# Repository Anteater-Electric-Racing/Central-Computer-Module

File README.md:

# Central Computer Module 

Main embedded firmware board for KZ 2025

## PCB Render

## Schematic

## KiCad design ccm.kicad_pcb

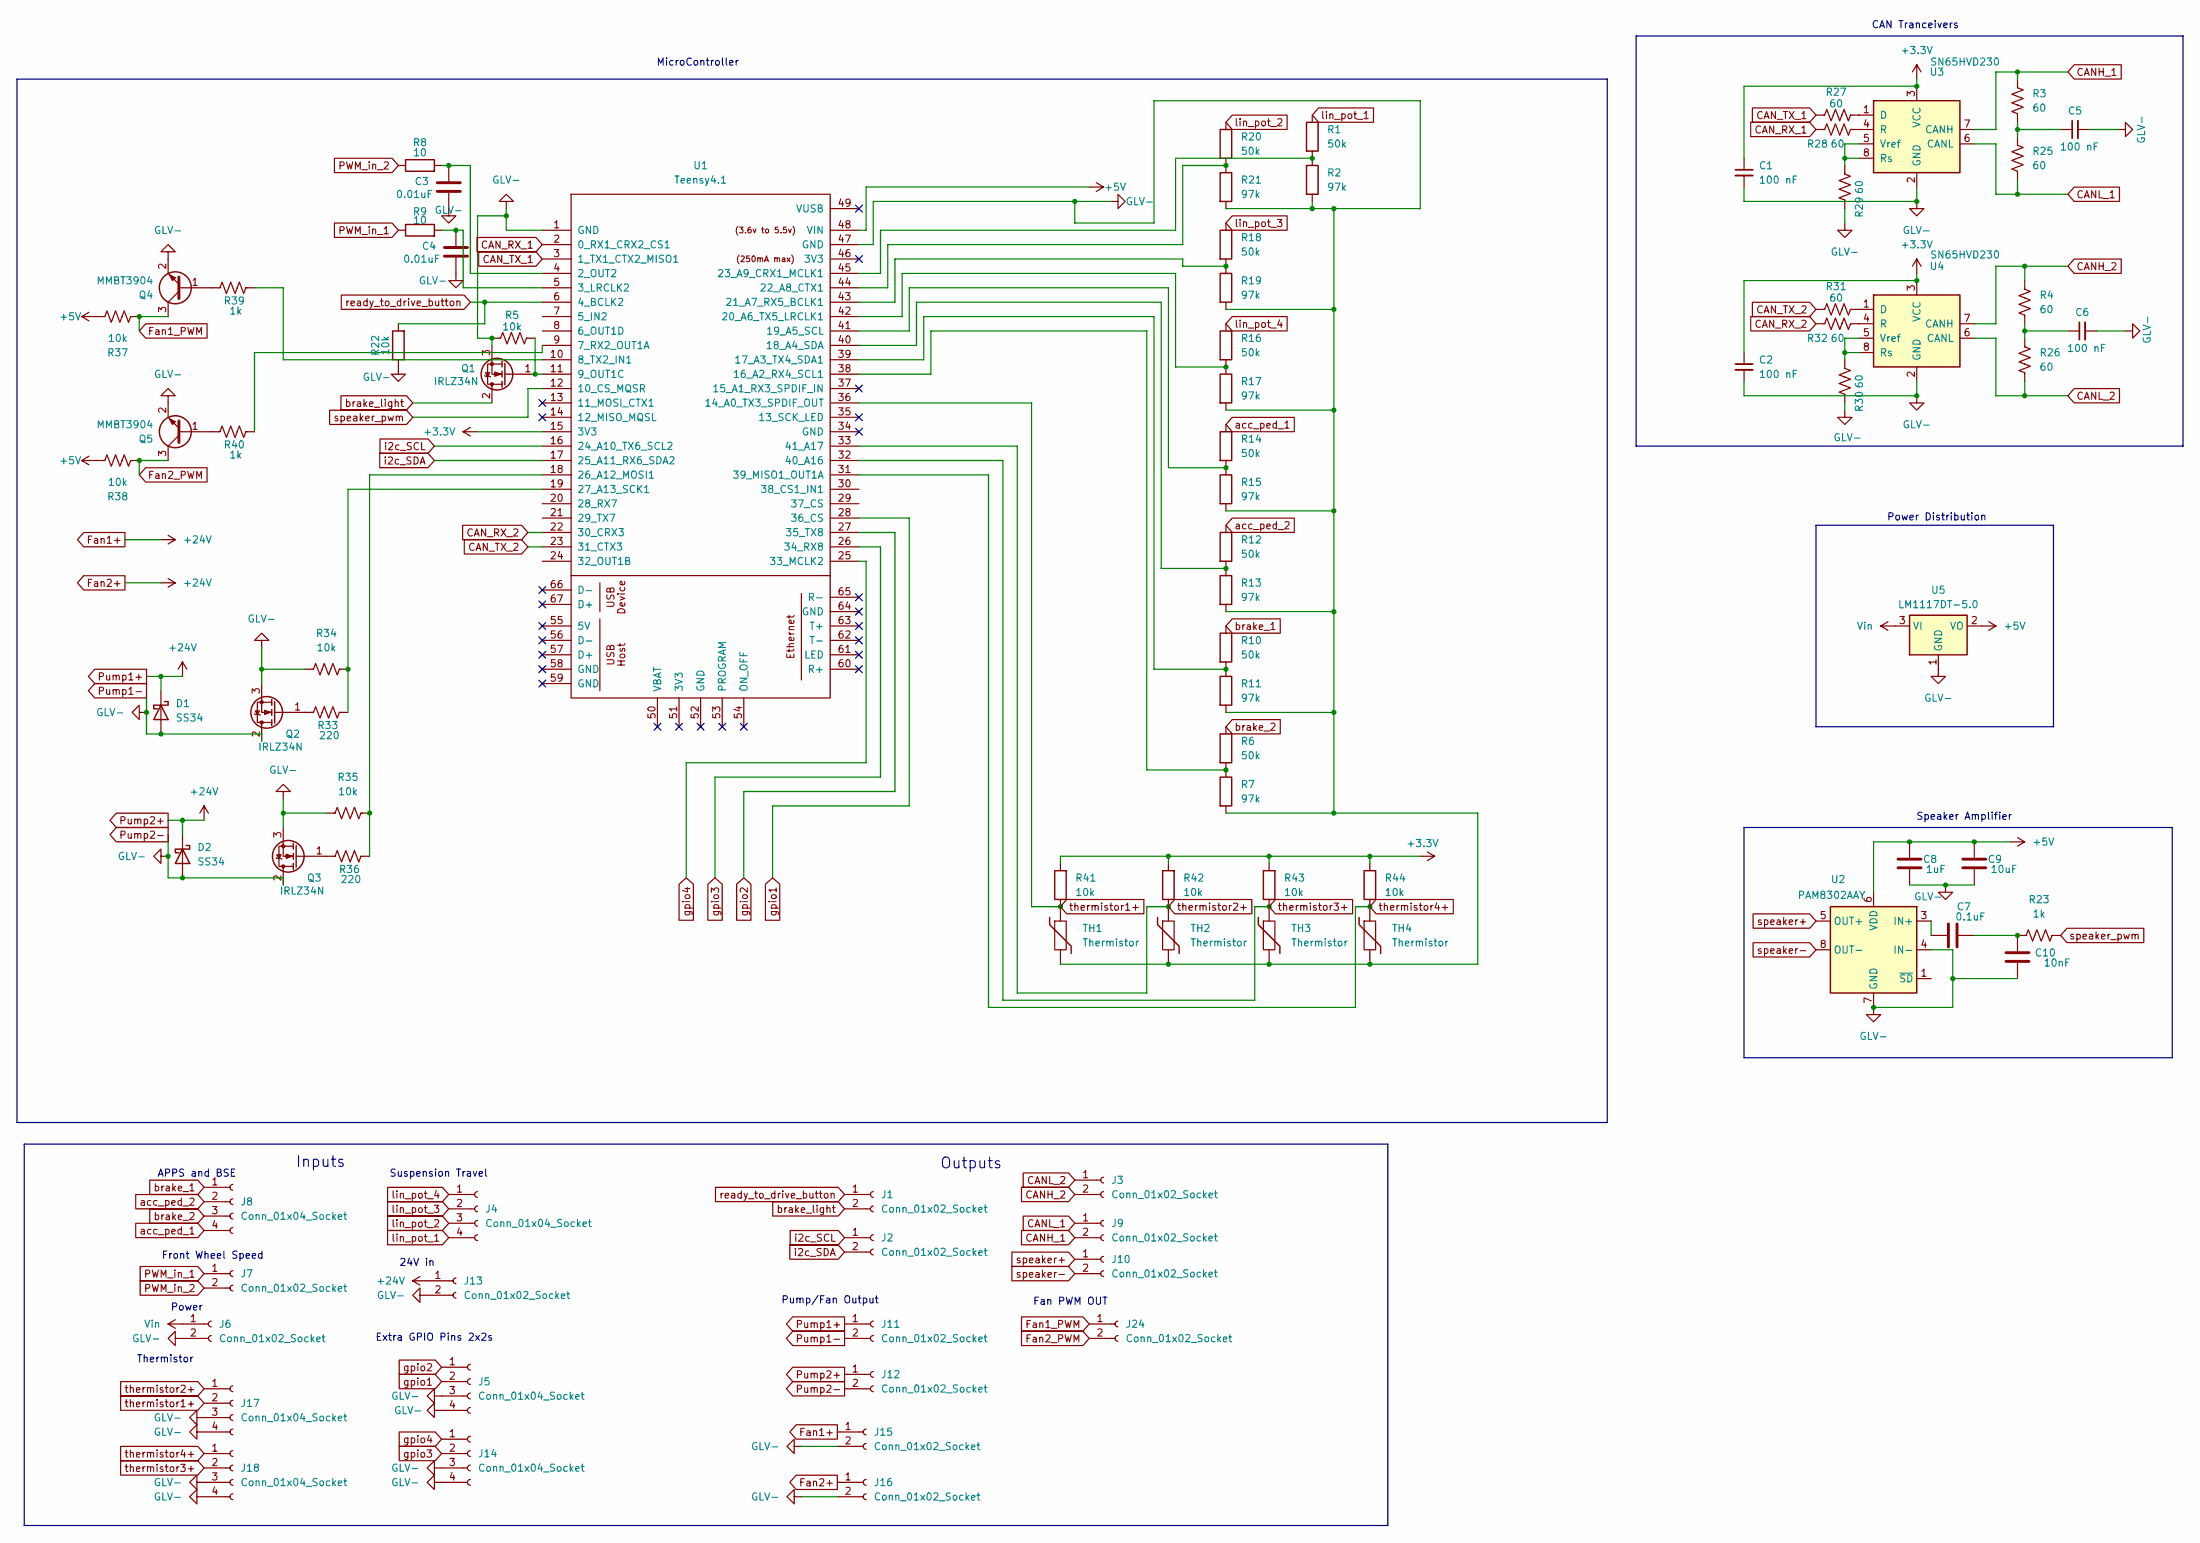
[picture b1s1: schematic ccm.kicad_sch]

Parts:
C1, C2, C5, C6: 100 nF; C_0805_2012Metric
C3, C4: 0.01uF; C_0805_2012Metric
C7: 0.1uF; C_0805_2012Metric
C8: 1uF; C_0805_2012Metric
C9: 10uF; C_0805_2012Metric
C10: 10nF; C_0805_2012Metric
D1, D2: SS34; D_SMA
J1, J2, J3, J6, J7, J9, J10, J11, J12, J13, J15, J16, J24: Conn_01x02_Socket; Molex_Mini-Fit_Jr_5566-02A2_2x01_P4.20mm_Vertical
J4, J5, J8, J14, J17, J18: Conn_01x04_Socket; Molex_Mini-Fit_Jr_5566-04A2_2x02_P4.20mm_Vertical
Q1, Q2, Q3: IRLZ34N; TO-220-3_Vertical
Q4, Q5: MMBT3904; SOT-23
R1, R6, R10, R12, R14, R16, R18, R20: 50k; R_0805_2012Metric
R2, R7, R11, R13, R15, R17, R19, R21: 97k; R_0805_2012Metric
R3, R4, R25, R26, R27, R28, R29, R30, R31, R32: 60; R_0805_2012Metric
R5, R22, R34, R35, R37, R38, R41, R42, R43, R44: 10k; R_0805_2012Metric
R8, R9: 10; R_0805_2012Metric
R23, R39, R40: 1k; R_0805_2012Metric
R33, R36: 220; R_0805_2012Metric
TH1, TH2, TH3, TH4: Thermistor
U1: Teensy4.1; CONN_4848-6000-CP_3MM
U2: PAM8302AAY; DFN-8-1EP_3x3mm_P0.65mm_EP1.55x2.4mm
U3, U4: SN65HVD230; SOIC-8_3.9x4.9mm_P1.27mm
U5: LM1117DT-5.0; TO-252-3_TabPin2

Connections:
+3.3V: C1.1, C2.1, R41.2, R42.2, R43.2, R44.2, U1.15 (3V3), U3.3 (VCC), U4.3 (VCC)
+5V: C8.1, C9.1, R37.1, R38.1, U1.48 (VIN), U2.6 (VDD), U5.2 (VO)
CANH_1: J9.2, R3.1, U3.7 (CANH)
CANH_2: J3.2, R4.1, U4.7 (CANH)
CANL_1: J9.1, R25.2, U3.6 (CANL)
CANL_2: J3.1, R26.2, U4.6 (CANL)
CAN_RX_1: R28.1, U1.2 (0_RX1_CRX2_CS1)
CAN_RX_2: R32.1, U1.22 (30_CRX3)
CAN_TX_1: R27.1, U1.3 (1_TX1_CTX2_MISO1)
CAN_TX_2: R31.1, U1.23 (31_CTX3)
Fan1+: D1.1 (K), D2.1 (K), J11.1, J12.1, J13.1, J15.1, J16.1
Fan1_PWM: J24.1, Q4.3 (C), R37.2
Fan2_PWM: J24.2, Q5.3 (C), R38.2
unnamed: C5.1, R3.2, R25.1
unnamed: C6.1, R4.2, R26.1
unnamed: C7.2, C10.2, R23.1
unnamed: Q1.1 (G), R5.2, U1.11 (9_OUT1C)
unnamed: Q2.1 (G), R33.1
unnamed: Q3.1 (G), R36.1
unnamed: Q4.1 (B), R39.1
unnamed: Q5.1 (B), R40.1
unnamed: C3.1, R8.2, U1.4 (2_OUT2)
unnamed: C4.1, R9.2, U1.5 (3_LRCLK2)
unnamed: R40.2, U1.9 (7_RX2_OUT1A)
unnamed: R39.2, U1.10 (8_TX2_IN1)
unnamed: R6.2, R7.1, U1.38 (16_A2_RX4_SCL1)
unnamed: R10.2, R11.1, U1.39 (17_A3_TX4_SDA1)
unnamed: R12.2, R13.1, U1.40 (18_A4_SDA)
unnamed: R14.2, R15.1, U1.41 (19_A5_SCL)
unnamed: R16.2, R17.1, U1.42 (20_A6_TX5_LRCLK1)
unnamed: R18.2, R19.1, U1.43 (21_A7_RX5_BCLK1)
unnamed: R20.2, R21.1, U1.44 (22_A8_CTX1)
unnamed: R1.2, R2.1, U1.45 (23_A9_CRX1_MCLK1)
unnamed: R35.1, R36.2, U1.18 (26_A12_MOSI1)
unnamed: R33.2, R34.1, U1.19 (27_A13_SCK1)
unnamed: C7.1, U2.3 (IN+)
unnamed: R27.2, U3.1 (D)
unnamed: R28.2, U3.4 (R)
unnamed: R29.2, U3.5 (Vref), U3.8 (Rs)
unnamed: R31.2, U4.1 (D)
unnamed: R32.2, U4.4 (R)
unnamed: R30.2, U4.5 (Vref), U4.8 (Rs)
PWM_in_1: J7.1, R9.1
PWM_in_2: J7.2, R8.1
Pump1-: C1.2, C2.2, C3.2, C4.2, C5.2, C6.2, C8.2, C9.2, C10.1, D1.2 (A), D2.2 (A), J5.3, J5.4, J6.2, J11.2, J12.2, J13.2, J14.3, J14.4, J15.2, J16.2, J17.3, J17.4, J18.3, J18.4, Q1.3 (S), Q2.2 (D), Q2.3 (S), Q3.2 (D), Q3.3 (S), Q4.2 (E), Q5.2 (E), R2.2, R5.1, R7.2, R11.2, R13.2, R15.2, R17.2, R19.2, R21.2, R22.1, R29.1, R30.1, R34.2, R35.2, TH1.2, TH2.2, TH3.2, TH4.2, U1.1 (GND), U1.47 (GND), U2.4 (IN-), U2.7 (GND), U3.2 (GND), U4.2 (GND), U5.1 (GND)
Vin: J6.1, U5.3 (VI)
acc_ped_1: J8.4, R14.1
acc_ped_2: J8.2, R12.1
brake_1: J8.1, R10.1
brake_2: J8.3, R6.1
brake_light: J1.2, Q1.2 (D)
gpio1: J5.2, U1.28 (36_CS)
gpio2: J5.1, U1.27 (35_TX8)
gpio3: J14.2, U1.26 (34_RX8)
gpio4: J14.1, U1.25 (33_MCLK2)
i2c_SCL: J2.1, U1.16 (24_A10_TX6_SCL2)
i2c_SDA: J2.2, U1.17 (25_A11_RX6_SDA2)
lin_pot_1: J4.4, R1.1
lin_pot_2: J4.3, R20.1
lin_pot_3: J4.2, R18.1
lin_pot_4: J4.1, R16.1
ready_to_drive_button: J1.1, R22.2, U1.6 (4_BCLK2)
speaker+: J10.1, U2.5 (OUT+)
speaker-: J10.2, U2.8 (OUT-)
speaker_pwm: R23.2, U1.12 (10_CS_MQSR)
thermistor1+: J17.2, R41.1, TH1.1, U1.36 (14_A0_TX3_SPDIF_OUT)
thermistor2+: J17.1, R42.1, TH2.1, U1.33 (41_A17)
thermistor3+: J18.2, R43.1, TH3.1, U1.32 (40_A16)
thermistor4+: J18.1, R44.1, TH4.1, U1.31 (39_MISO1_OUT1A)

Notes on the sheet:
Suspension Travel
APPS and BSE
Power
Extra GPIO Pins 2x2s
Front Wheel Speed
Inputs
Fan PWM OUT
Power Distribution
24V in
Speaker Amplifier
Thermistor
Outputs
Pump/Fan Output
CAN Tranceivers
MicroController

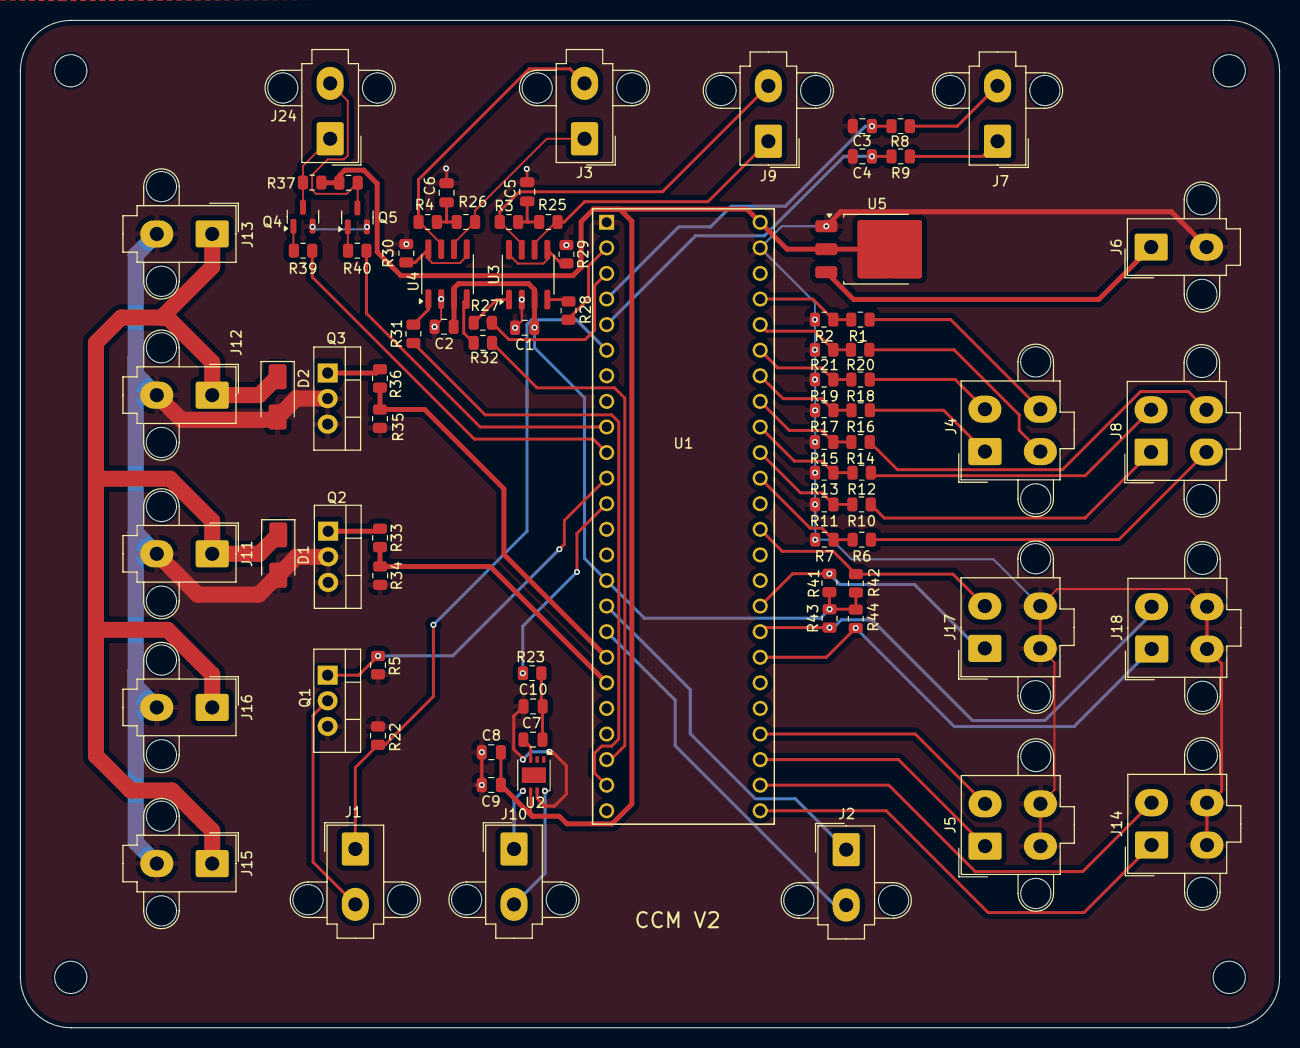
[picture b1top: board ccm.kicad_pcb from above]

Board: 2 copper layers, 125.0 x 100.0 mm, 84 parts (0 on the bottom side), 69 nets.

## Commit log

2025-01-30 renamed copy of cvb + layout v1
2025-01-31 added DIP socket connector for teensy
2025-01-31 add edge cuts; begin routing v1
2025-02-01 routing finished
2025-02-01 change brake and accel connectors
2025-02-01 redo layout
2025-02-02 add bottom gnd zone
2025-02-02 add readme
2025-02-02 fix mounting holes
2025-02-02 thicken power trace widths
2025-02-05 remove 5v/glv from throttle/brake sensors
2025-02-05 update routing
2025-02-13 add mosfet for brake light output and decoupling capacitors
2025-02-13 backup commit (no split termination or speaker amp)
2025-02-13 changed voltage divider to use 2 resistors
2025-02-13 right side routed
2025-02-13 finish new routing
    Todo (serial resistors)
2025-02-14 added serial resistors to CAN tranciever
2025-02-14 add step files for molex
2025-02-14 update bom
2025-02-15 added capacitors for amp
2025-02-15 added speaker notes
2025-02-16 added gerber files
2025-04-17 updated to revision schematic
    tbd i/o connectors
2025-04-17 add i/o connectors
    tbd pcb revision
2025-04-24 ccm schem complete
2025-04-29 layout v1
2025-05-01 add npn transistor level shifter for fan pwm
2025-05-01 leftside routing complete
2025-05-01 routing v2.1 complete
2025-05-06 v2 fixes complete
2025-12-18 Organization Update
2025-12-19 Fix image paths in README.md
    Updated image paths in README for documentation structure.
2026-02-21 added 3d models
